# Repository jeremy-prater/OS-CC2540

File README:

OS CC-2540

Directory Structure

\Final Design.png -- Start here to see how the board is layed out
\BLE v1.0 prater mod.sch -- HM-10 Host board schematic
\BLE v1.0 prater mod.brd -- HM-10 Host board layout
\OSCC2540 - BOM.csv -- HM-10 Host board Bill Of Materials
\ATMega 328 SPI\ATMega 328 SPI.atsln -- ATMega 328 Firmware Project file for ATMEL Studio 6.2
\HM-10 Hack\HM-10 Firmware\Projects\ble\HostTestApp\CC2540\HostTestRelease.eww -- IAR Project file for CC2540 firmware
\Interface Board\Interface Board.zdsproj -- Project file for Zilog interface board
\HM-10 SDI\HM-10 SDI.sln -- Visual Studio 2013 project for windows interface to OS-CC2540

Best steps to start prototyping the firmware

Look over the Final Design.png
Look over Board schematic and layout
Order BOM parts
Order HM-10 Host Board from OSH Park
Build Board
Flash ATMega Firmware
Flash CC2540 Firmware
Start Issuing Commands via SPI to HM-10 Host Board

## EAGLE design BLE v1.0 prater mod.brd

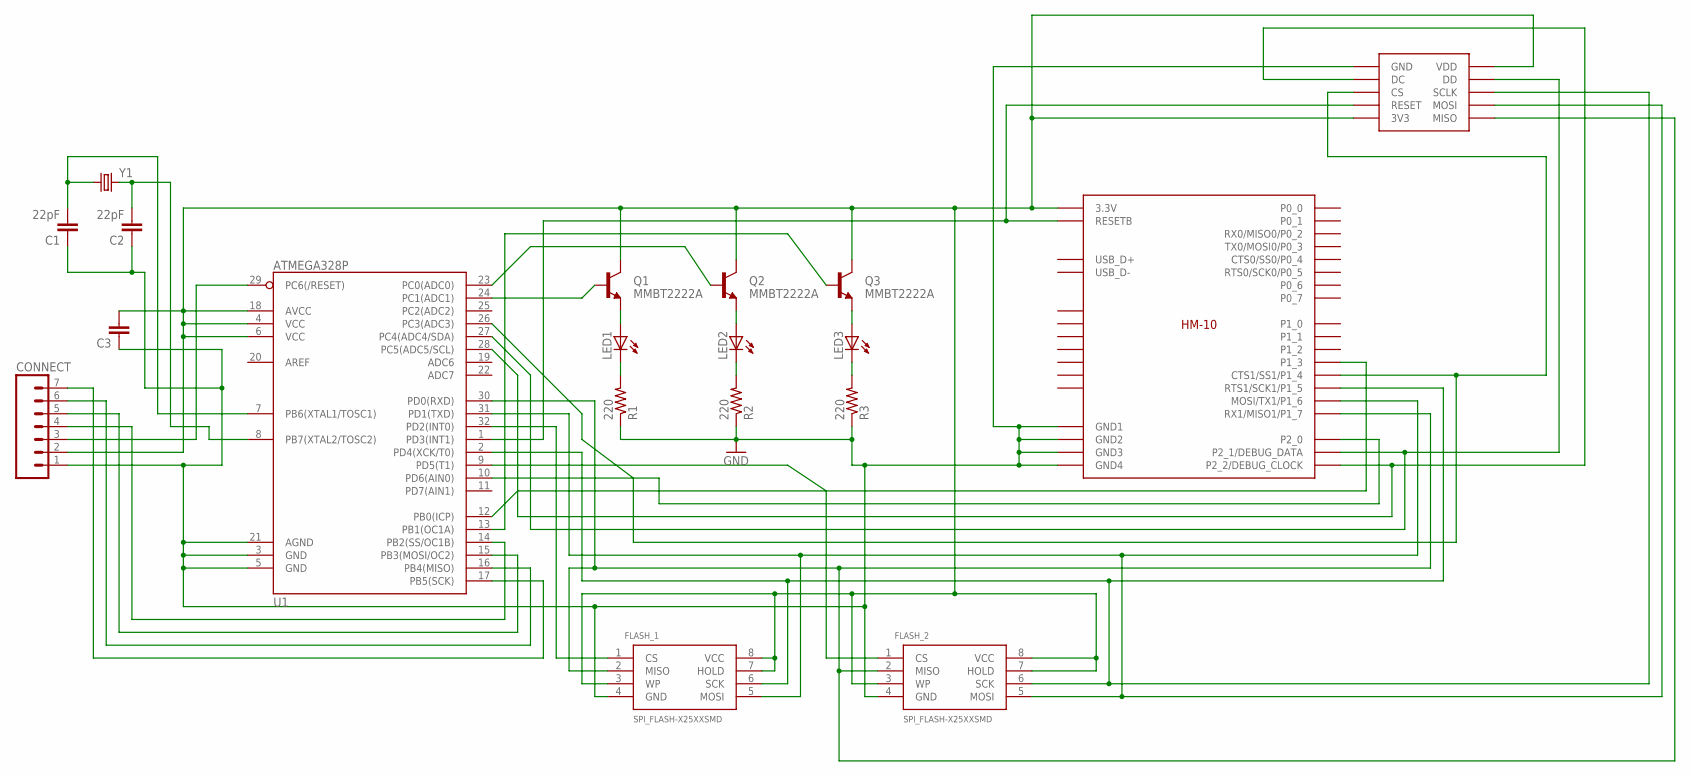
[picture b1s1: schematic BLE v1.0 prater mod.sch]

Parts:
C1, C2: 22pF; 0603-CAP
C3: CAP1210; 1210
CONNECT: M07; 1X07
FLASH_1, FLASH_2: SPI_FLASH-X25XXSMD; SO08
LED1, LED2, LED3: LED0603; LED-0603
Q1, Q2, Q3: MMBT2222A; SOT23
R1, R2, R3: 220; M0805
U1: ATMEGA328P; TQFP32-08
U$1: BLE-HM-10
U$4: 2X5-.127-HEADER
Y1: CRYSTALHC49US; HC49US

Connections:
3V3: C3.2, CONNECT.2, FLASH_1.3 (WP), FLASH_1.7 (HOLD), FLASH_1.8 (VCC), FLASH_2.3 (WP), FLASH_2.7 (HOLD), FLASH_2.8 (VCC), Q1.3 (C), Q2.3 (C), Q3.3 (C), U1.4 (VCC), U1.6 (VCC), U1.18 (AVCC), U$1.3.3V, U$4.3V3, U$4.VDD
GND: C1.1, C2.1, C3.1, CONNECT.1, FLASH_1.4 (GND), FLASH_2.4 (GND), R1.1, R2.1, R3.1, U1.3 (GND), U1.5 (GND), U1.21 (AGND), U$1.GND1, U$1.GND2, U$1.GND3, U$1.GND4, U$4.GND
unnamed: LED3.A, Q3.2 (E)
unnamed: LED1.A, Q1.2 (E)
unnamed: FLASH_1.6 (SCK), FLASH_2.6 (SCK), U1.2 (PD4(XCK/T0)), U$1.UART_RTS (RTS1/SCK1/P1_5), U$4.SCLK
unnamed: FLASH_1.2 (MISO), FLASH_2.2 (MISO), U1.30 (PD0(RXD)), U$1.UART_RX (RX1/MISO1/P1_7), U$4.MISO
unnamed: LED1.C, R1.2
unnamed: FLASH_1.5 (MOSI), FLASH_2.5 (MOSI), U1.31 (PD1(TXD)), U$1.UART_TX (MOSI/TX1/P1_6), U$4.MOSI
unnamed: CONNECT.6, U1.16 (PB4(MISO))
unnamed: LED2.A, Q2.2 (E)
unnamed: LED3.C, R3.2
unnamed: FLASH_2.1 (CS), U1.9 (PD5(T1))
unnamed: C2.2, U1.8 (PB7(XTAL2/TOSC2)), Y1.2
unnamed: Q2.1 (B), U1.23 (PC0(ADC0))
unnamed: Q3.1 (B), U1.13 (PB1(OC1A))
unnamed: FLASH_1.1 (CS), U1.32 (PD2(INT0))
unnamed: U1.26 (PC3(ADC3)), U$1.UART_CTS (CTS1/SS1/P1_4), U$4.CS
unnamed: CONNECT.7, U1.17 (PB5(SCK))
unnamed: CONNECT.5, U1.15 (PB3(MOSI/OC2))
unnamed: U1.1 (PD3(INT1)), U$1.RESET (RESETB), U$4.RESET
unnamed: LED2.C, R2.2
unnamed: U1.27 (PC4(ADC4/SDA)), U$1.PCM_SYNC (P2_1/DEBUG_DATA), U$4.DD
unnamed: U1.28 (PC5(ADC5/SCL)), U$1.PCM_IN (P2_2/DEBUG_CLOCK), U$4.DC
unnamed: CONNECT.4, U1.14 (PB2(SS/OC1B))
unnamed: CONNECT.3, U1.29 (PC6(/RESET))
unnamed: C1.2, U1.7 (PB6(XTAL1/TOSC1)), Y1.1
unnamed: Q1.1 (B), U1.24 (PC1(ADC1))
unnamed: U1.10 (PD6(AIN0)), U$1.AIO0 (P2_0)
unnamed: U1.12 (PB0(ICP)), U$1.PIO0 (P1_3)

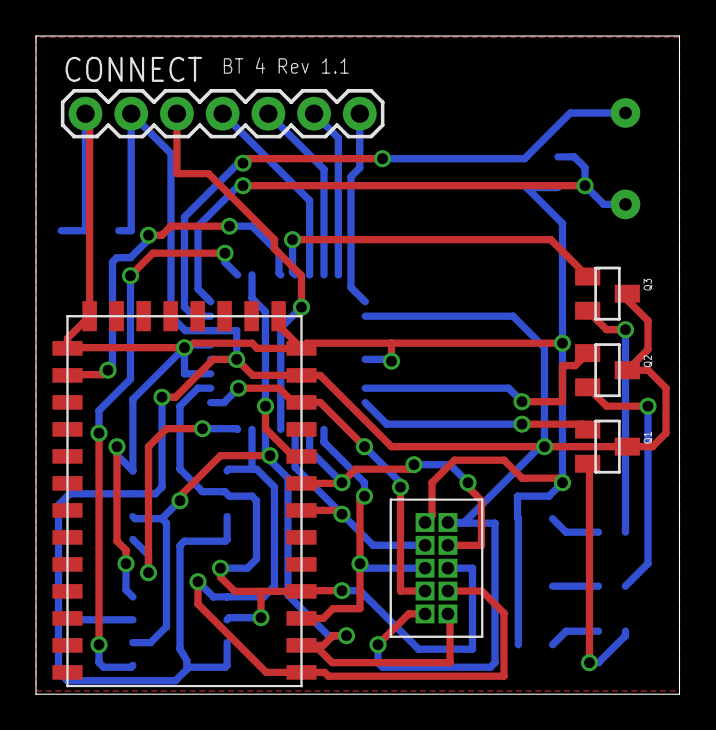
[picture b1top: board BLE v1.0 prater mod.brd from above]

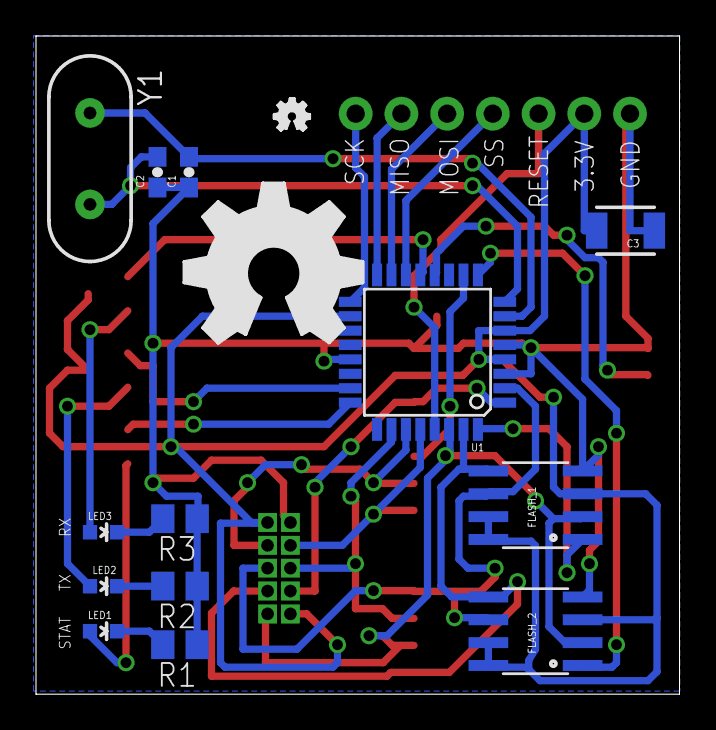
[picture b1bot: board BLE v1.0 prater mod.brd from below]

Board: 2 copper layers, 35.8 x 36.6 mm, 21 parts (15 on the bottom side), 29 nets.

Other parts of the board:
U$2: OSHW_FILLX350_NOTEXT
U$3: OSHW_FILLX70_NOTEXT

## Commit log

2014-11-09 :neckbeard: Added .gitattributes
2014-11-10 Initial Commit
    OS CC 2540 Beta Testing v0.9
2014-11-10 Bill of materials
    Digikey parts BOM file.

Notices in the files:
parts and their libraries:
SparkFun: Licensing: CC v3.0 Share-Alike You are welcome to use this library for commercial purposes.
